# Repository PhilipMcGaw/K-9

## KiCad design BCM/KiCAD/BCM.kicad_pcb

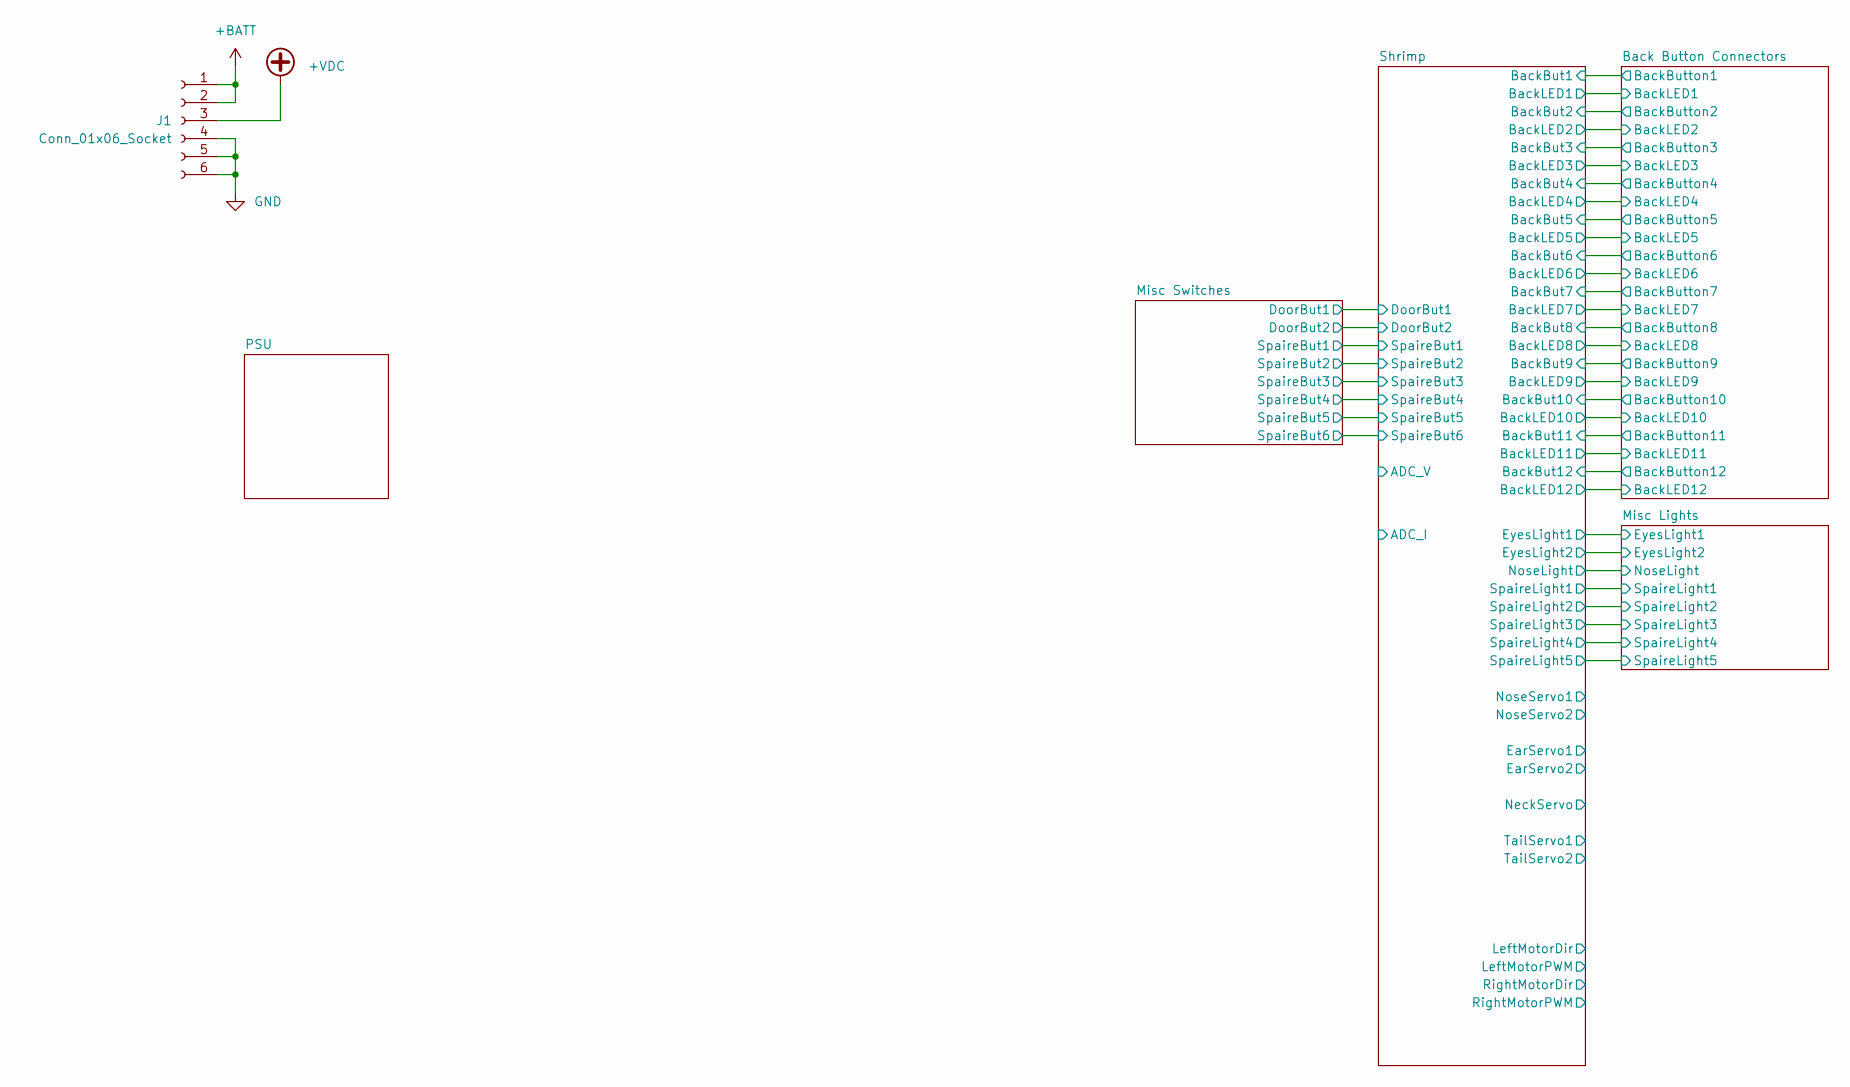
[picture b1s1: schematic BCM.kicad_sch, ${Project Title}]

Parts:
J1: Conn_01x06_Socket

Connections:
unnamed: J1.1, J1.2
unnamed: J1.4, J1.5, J1.6

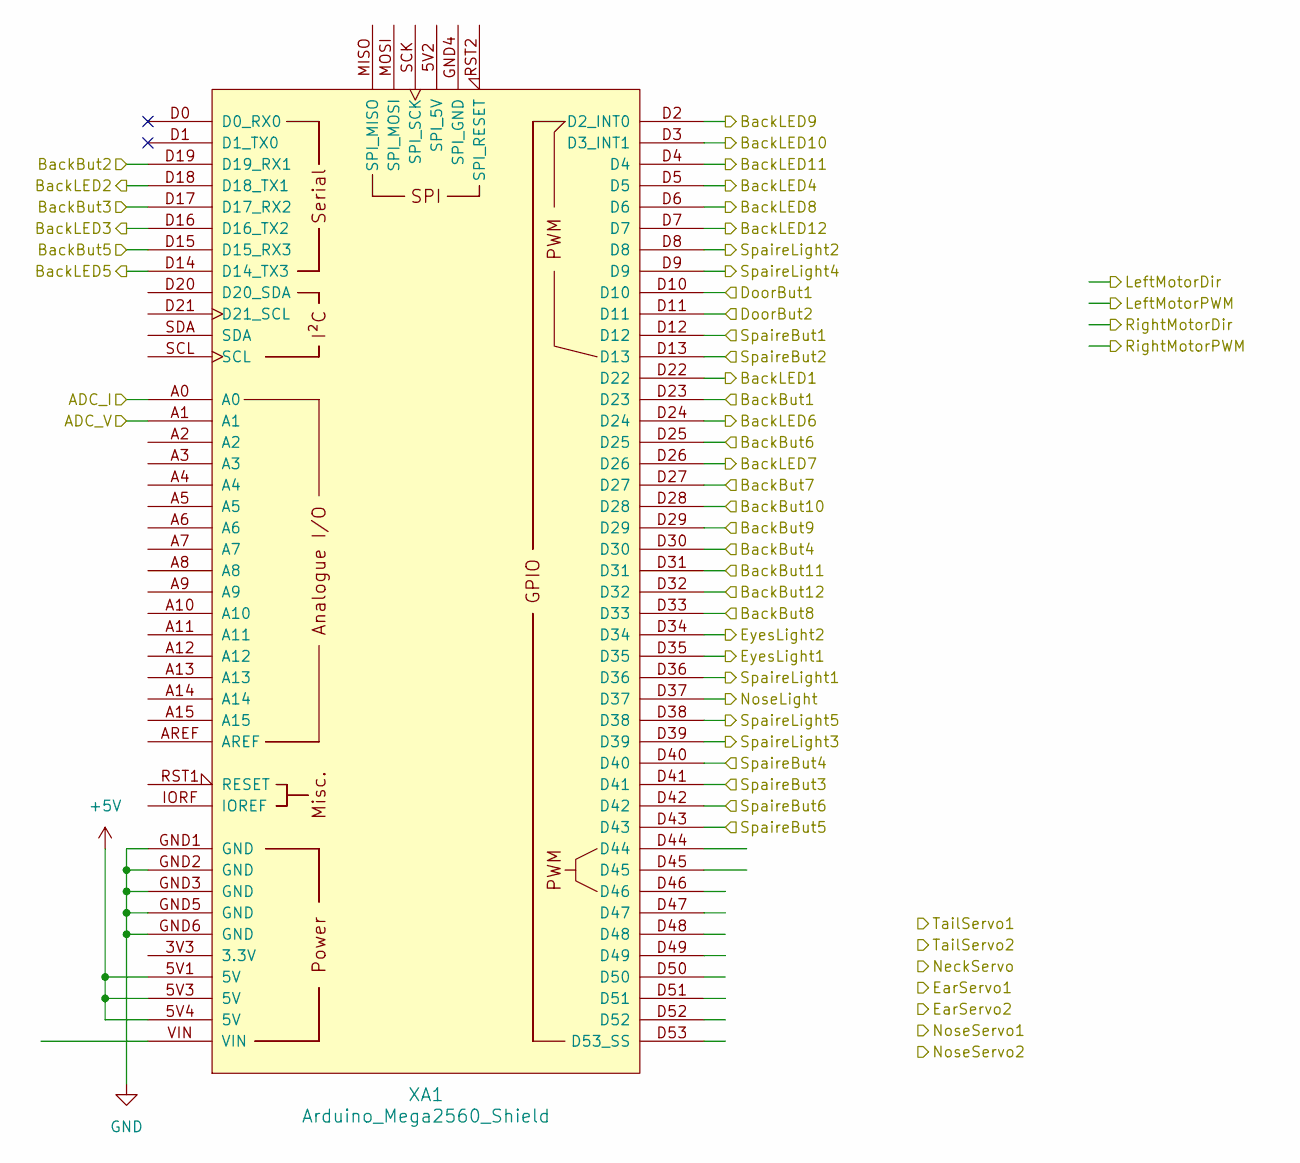
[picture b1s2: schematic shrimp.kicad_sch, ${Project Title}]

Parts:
XA1: Arduino_Mega2560_Shield

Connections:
+5V: XA1.5V1 (5V), XA1.5V3 (5V), XA1.5V4 (5V); also elsewhere on the board
/Back Button Connectors/BackButton1: XA1.D23; also elsewhere on the board
/Back Button Connectors/BackButton2: XA1.D19 (D19_RX1); also elsewhere on the board
/Back Button Connectors/BackButton3: XA1.D17 (D17_RX2); also elsewhere on the board
/Back Button Connectors/BackButton4: XA1.D30; also elsewhere on the board
/Back Button Connectors/BackButton5: XA1.D15 (D15_RX3); also elsewhere on the board
/Back Button Connectors/BackButton6: XA1.D25; also elsewhere on the board
/Back Button Connectors/BackButton7: XA1.D27; also elsewhere on the board
/Back Button Connectors/BackButton8: XA1.D33; also elsewhere on the board
/Back Button Connectors/BackButton9: XA1.D29; also elsewhere on the board
/Back Button Connectors/BackButton10: XA1.D28; also elsewhere on the board
/Back Button Connectors/BackButton11: XA1.D31; also elsewhere on the board
/Back Button Connectors/BackButton12: XA1.D32; also elsewhere on the board
/Back Button Connectors/BackLED1: XA1.D22; also elsewhere on the board
/Back Button Connectors/BackLED2: XA1.D18 (D18_TX1); also elsewhere on the board
/Back Button Connectors/BackLED3: XA1.D16 (D16_TX2); also elsewhere on the board
/Back Button Connectors/BackLED4: XA1.D5; also elsewhere on the board
/Back Button Connectors/BackLED5: XA1.D14 (D14_TX3); also elsewhere on the board
/Back Button Connectors/BackLED6: XA1.D24; also elsewhere on the board
/Back Button Connectors/BackLED7: XA1.D26; also elsewhere on the board
/Back Button Connectors/BackLED8: XA1.D6; also elsewhere on the board
/Back Button Connectors/BackLED9: XA1.D2 (D2_INT0); also elsewhere on the board
/Back Button Connectors/BackLED10: XA1.D3 (D3_INT1); also elsewhere on the board
/Back Button Connectors/BackLED11: XA1.D4; also elsewhere on the board
/Back Button Connectors/BackLED12: XA1.D7; also elsewhere on the board
/Misc Lights/EyesLight1: XA1.D35; also elsewhere on the board
/Misc Lights/EyesLight2: XA1.D34; also elsewhere on the board
/Misc Lights/NoseLight: XA1.D37; also elsewhere on the board
/Misc Lights/SpaireLight1: XA1.D36; also elsewhere on the board
/Misc Lights/SpaireLight2: XA1.D8; also elsewhere on the board
/Misc Lights/SpaireLight3: XA1.D39; also elsewhere on the board
/Misc Lights/SpaireLight4: XA1.D9; also elsewhere on the board
/Misc Lights/SpaireLight5: XA1.D38; also elsewhere on the board
/Misc Switches/DoorBut1: XA1.D10; also elsewhere on the board
/Misc Switches/DoorBut2: XA1.D11; also elsewhere on the board
/Misc Switches/SpaireBut1: XA1.D12; also elsewhere on the board
/Misc Switches/SpaireBut2: XA1.D13; also elsewhere on the board
/Misc Switches/SpaireBut3: XA1.D41; also elsewhere on the board
/Misc Switches/SpaireBut4: XA1.D40; also elsewhere on the board
/Misc Switches/SpaireBut5: XA1.D43; also elsewhere on the board
/Misc Switches/SpaireBut6: XA1.D42; also elsewhere on the board
/Shrimp/ADC_I: XA1.A0
/Shrimp/ADC_V: XA1.A1
/Shrimp/EarServo1: XA1.D50
/Shrimp/EarServo2: XA1.D51
/Shrimp/NeckServo: XA1.D49
/Shrimp/NoseServo1: XA1.D52
/Shrimp/NoseServo2: XA1.D53 (D53_SS)
/Shrimp/SpairServo1: XA1.D44
/Shrimp/SpairServo2: XA1.D45
/Shrimp/SpairServo3: XA1.D46
/Shrimp/TailServo1: XA1.D47
/Shrimp/TailServo2: XA1.D48
GND: XA1.GND1 (GND), XA1.GND2 (GND), XA1.GND3 (GND), XA1.GND5 (GND), XA1.GND6 (GND); also elsewhere on the board

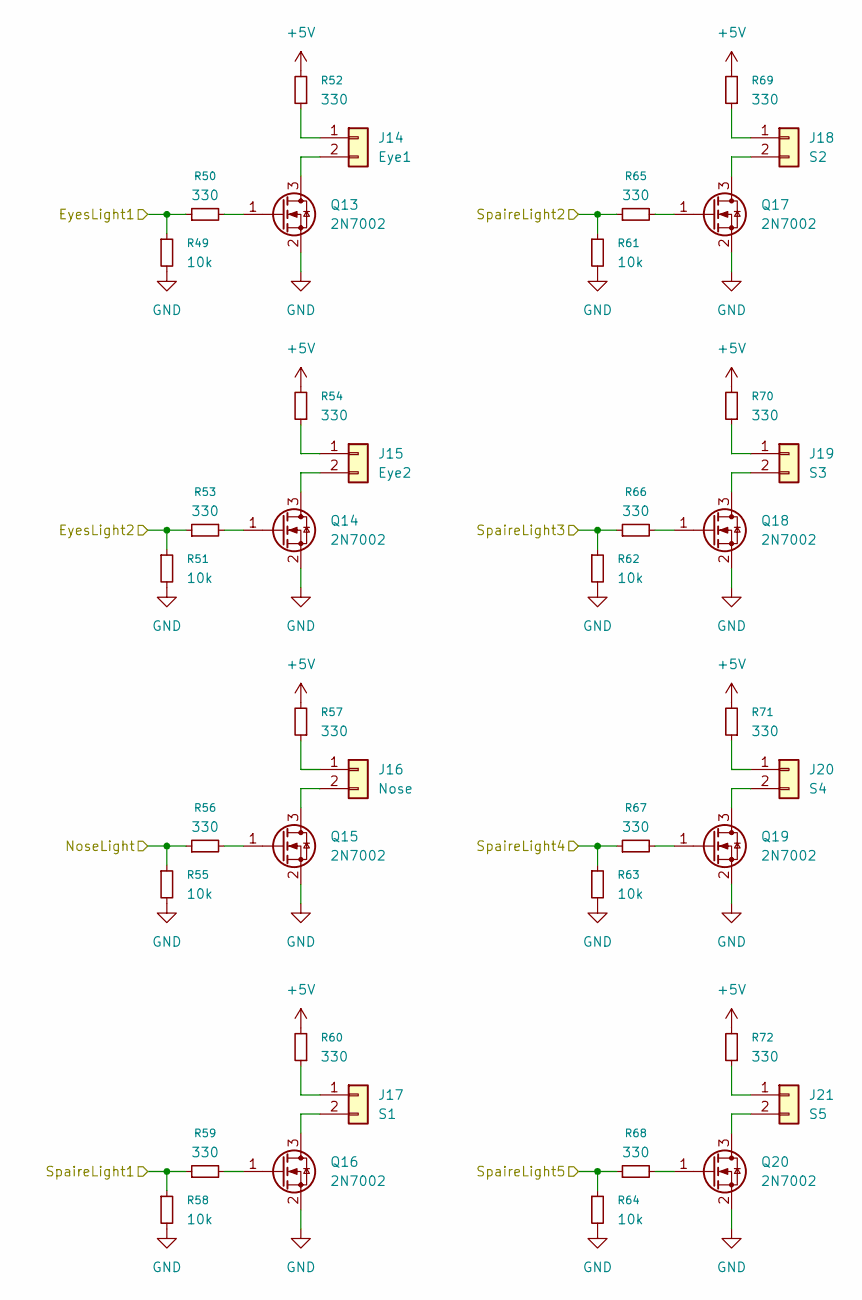
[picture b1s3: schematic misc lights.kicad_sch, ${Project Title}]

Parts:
J14: Eye1; JST_XA_B02B-XASK-1_1x02_P2.50mm_Vertical
J15: Eye2; JST_XA_B02B-XASK-1_1x02_P2.50mm_Vertical
J16: Nose; JST_XA_B02B-XASK-1_1x02_P2.50mm_Vertical
J17: S1; JST_XA_B02B-XASK-1_1x02_P2.50mm_Vertical
J18: S2; JST_XA_B02B-XASK-1_1x02_P2.50mm_Vertical
J19: S3; JST_XA_B02B-XASK-1_1x02_P2.50mm_Vertical
J20: S4; JST_XA_B02B-XASK-1_1x02_P2.50mm_Vertical
J21: S5; JST_XA_B02B-XASK-1_1x02_P2.50mm_Vertical
Q13, Q14, Q15, Q16, Q17, Q18, Q19, Q20: 2N7002; SOT-23
R49, R51, R55, R58, R61, R62, R63, R64: 10k; R_0805_2012Metric_Pad1.20x1.40mm_HandSolder
R50, R52, R53, R54, R56, R57, R59, R60, R65, R66, R67, R68, R69, R70, R71, R72: 330; R_0805_2012Metric_Pad1.20x1.40mm_HandSolder

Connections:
+5V: R52.2, R54.2, R57.2, R60.2, R69.2, R70.2, R71.2, R72.2; also elsewhere on the board
/Misc Lights/EyesLight1: R49.1, R50.1; also elsewhere on the board
/Misc Lights/EyesLight2: R51.1, R53.1; also elsewhere on the board
/Misc Lights/NoseLight: R55.1, R56.1; also elsewhere on the board
/Misc Lights/SpaireLight1: R58.1, R59.1; also elsewhere on the board
/Misc Lights/SpaireLight2: R61.1, R65.1; also elsewhere on the board
/Misc Lights/SpaireLight3: R62.1, R66.1; also elsewhere on the board
/Misc Lights/SpaireLight4: R63.1, R67.1; also elsewhere on the board
/Misc Lights/SpaireLight5: R64.1, R68.1; also elsewhere on the board
GND: Q13.2 (S), Q14.2 (S), Q15.2 (S), Q16.2 (S), Q17.2 (S), Q18.2 (S), Q19.2 (S), Q20.2 (S), R49.2, R51.2, R55.2, R58.2, R61.2, R62.2, R63.2, R64.2; also elsewhere on the board
unnamed: J14.1, R52.1
unnamed: J14.2, Q13.3 (D)
unnamed: J15.1, R54.1
unnamed: J15.2, Q14.3 (D)
unnamed: J16.1, R57.1
unnamed: J16.2, Q15.3 (D)
unnamed: J17.1, R60.1
unnamed: J17.2, Q16.3 (D)
unnamed: J18.1, R69.1
unnamed: J18.2, Q17.3 (D)
unnamed: J19.1, R70.1
unnamed: J19.2, Q18.3 (D)
unnamed: J20.1, R71.1
unnamed: J20.2, Q19.3 (D)
unnamed: J21.1, R72.1
unnamed: J21.2, Q20.3 (D)
unnamed: Q13.1 (G), R50.2
unnamed: Q14.1 (G), R53.2
unnamed: Q15.1 (G), R56.2
unnamed: Q16.1 (G), R59.2
unnamed: Q17.1 (G), R65.2
unnamed: Q18.1 (G), R66.2
unnamed: Q19.1 (G), R67.2
unnamed: Q20.1 (G), R68.2

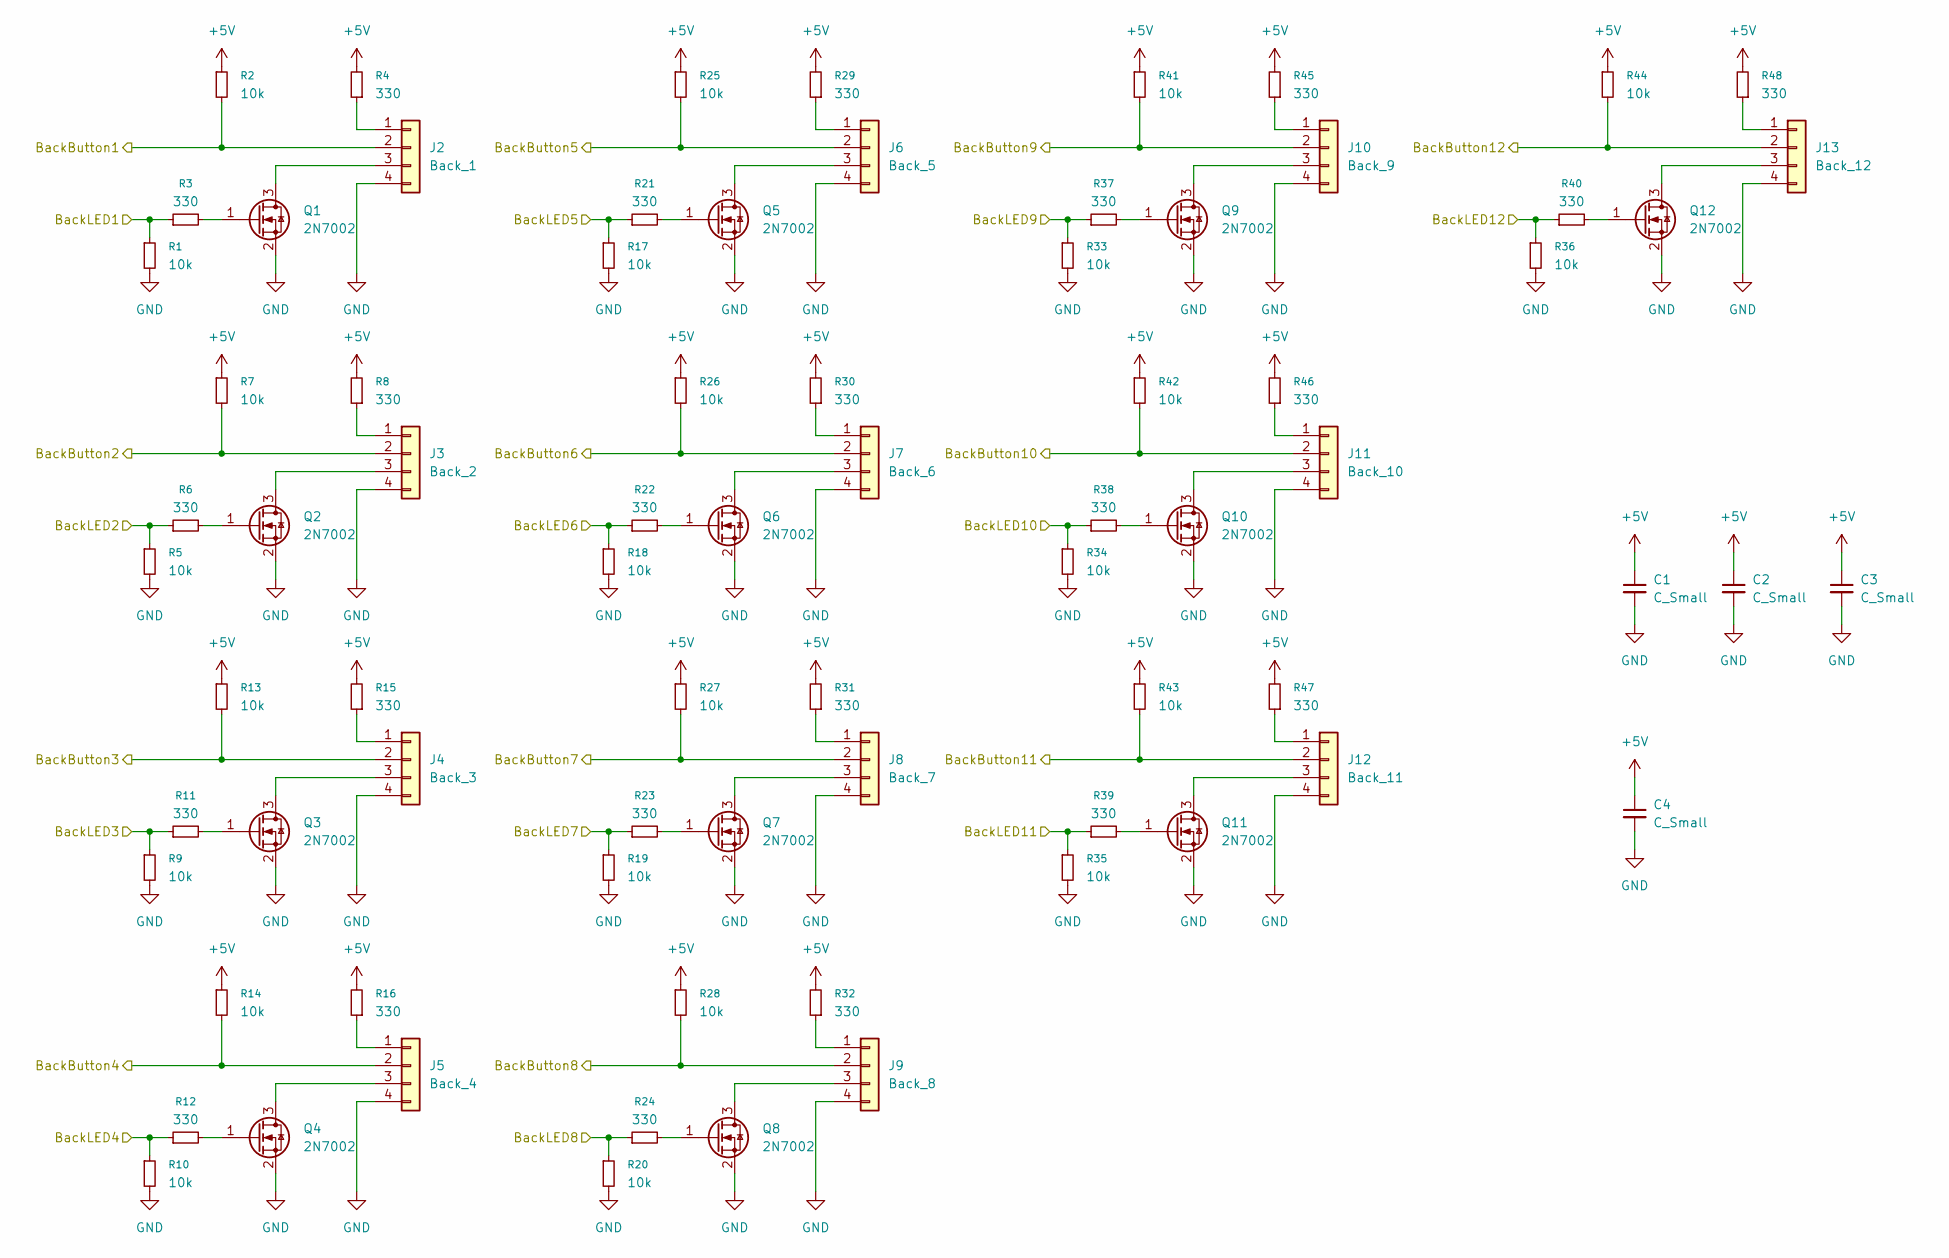
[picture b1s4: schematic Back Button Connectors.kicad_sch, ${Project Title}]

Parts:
C1, C2, C3, C4: C_Small; C_0805_2012Metric_Pad1.18x1.45mm_HandSolder
J2: Back_1; JST_XA_B04B-XASK-1_1x04_P2.50mm_Vertical
J3: Back_2; JST_XA_B04B-XASK-1_1x04_P2.50mm_Vertical
J4: Back_3; JST_XA_B04B-XASK-1_1x04_P2.50mm_Vertical
J5: Back_4; JST_XA_B04B-XASK-1_1x04_P2.50mm_Vertical
J6: Back_5; JST_XA_B04B-XASK-1_1x04_P2.50mm_Vertical
J7: Back_6; JST_XA_B04B-XASK-1_1x04_P2.50mm_Vertical
J8: Back_7; JST_XA_B04B-XASK-1_1x04_P2.50mm_Vertical
J9: Back_8; JST_XA_B04B-XASK-1_1x04_P2.50mm_Vertical
J10: Back_9; JST_XA_B04B-XASK-1_1x04_P2.50mm_Vertical
J11: Back_10; JST_XA_B04B-XASK-1_1x04_P2.50mm_Vertical
J12: Back_11; JST_XA_B04B-XASK-1_1x04_P2.50mm_Vertical
J13: Back_12; JST_XA_B04B-XASK-1_1x04_P2.50mm_Vertical
Q1, Q2, Q3, Q4, Q5, Q6, Q7, Q8, Q9, Q10, Q11, Q12: 2N7002; SOT-23
R1, R2, R5, R7, R9, R10, R13, R14, R17, R18, R19, R20, R25, R26, R27, R28, R33, R34, R35, R36, R41, R42, R43, R44: 10k; R_0805_2012Metric_Pad1.20x1.40mm_HandSolder
R3, R4, R6, R8, R11, R12, R15, R16, R21, R22, R23, R24, R29, R30, R31, R32, R37, R38, R39, R40, R45, R46, R47, R48: 330; R_0805_2012Metric_Pad1.20x1.40mm_HandSolder

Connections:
+5V: C1.1, C2.1, C3.1, C4.1, R2.1, R4.2, R7.1, R8.2, R13.1, R14.1, R15.2, R16.2, R25.1, R26.1, R27.1, R28.1, R29.2, R30.2, R31.2, R32.2, R41.1, R42.1, R43.1, R44.1, R45.2, R46.2, R47.2, R48.2; also elsewhere on the board
/Back Button Connectors/BackButton1: J2.2, R2.2; also elsewhere on the board
/Back Button Connectors/BackButton2: J3.2, R7.2; also elsewhere on the board
/Back Button Connectors/BackButton3: J4.2, R13.2; also elsewhere on the board
/Back Button Connectors/BackButton4: J5.2, R14.2; also elsewhere on the board
/Back Button Connectors/BackButton5: J6.2, R25.2; also elsewhere on the board
/Back Button Connectors/BackButton6: J7.2, R26.2; also elsewhere on the board
/Back Button Connectors/BackButton7: J8.2, R27.2; also elsewhere on the board
/Back Button Connectors/BackButton8: J9.2, R28.2; also elsewhere on the board
/Back Button Connectors/BackButton9: J10.2, R41.2; also elsewhere on the board
/Back Button Connectors/BackButton10: J11.2, R42.2; also elsewhere on the board
/Back Button Connectors/BackButton11: J12.2, R43.2; also elsewhere on the board
/Back Button Connectors/BackButton12: J13.2, R44.2; also elsewhere on the board
/Back Button Connectors/BackLED1: R1.1, R3.1; also elsewhere on the board
/Back Button Connectors/BackLED2: R5.1, R6.1; also elsewhere on the board
/Back Button Connectors/BackLED3: R9.1, R11.1; also elsewhere on the board
/Back Button Connectors/BackLED4: R10.1, R12.1; also elsewhere on the board
/Back Button Connectors/BackLED5: R17.1, R21.1; also elsewhere on the board
/Back Button Connectors/BackLED6: R18.1, R22.1; also elsewhere on the board
/Back Button Connectors/BackLED7: R19.1, R23.1; also elsewhere on the board
/Back Button Connectors/BackLED8: R20.1, R24.1; also elsewhere on the board
/Back Button Connectors/BackLED9: R33.1, R37.1; also elsewhere on the board
/Back Button Connectors/BackLED10: R34.1, R38.1; also elsewhere on the board
/Back Button Connectors/BackLED11: R35.1, R39.1; also elsewhere on the board
/Back Button Connectors/BackLED12: R36.1, R40.1; also elsewhere on the board
GND: C1.2, C2.2, C3.2, C4.2, J2.4, J3.4, J4.4, J5.4, J6.4, J7.4, J8.4, J9.4, J10.4, J11.4, J12.4, J13.4, Q1.2 (S), Q2.2 (S), Q3.2 (S), Q4.2 (S), Q5.2 (S), Q6.2 (S), Q7.2 (S), Q8.2 (S), Q9.2 (S), Q10.2 (S), Q11.2 (S), Q12.2 (S), R1.2, R5.2, R9.2, R10.2, R17.2, R18.2, R19.2, R20.2, R33.2, R34.2, R35.2, R36.2; also elsewhere on the board
unnamed: J2.1, R4.1
unnamed: J2.3, Q1.3 (D)
unnamed: J3.1, R8.1
unnamed: J3.3, Q2.3 (D)
unnamed: J4.1, R15.1
unnamed: J4.3, Q3.3 (D)
unnamed: J5.1, R16.1
unnamed: J5.3, Q4.3 (D)
unnamed: J6.1, R29.1
unnamed: J6.3, Q5.3 (D)
unnamed: J7.1, R30.1
unnamed: J7.3, Q6.3 (D)
unnamed: J8.1, R31.1
unnamed: J8.3, Q7.3 (D)
unnamed: J9.1, R32.1
unnamed: J9.3, Q8.3 (D)
unnamed: J10.1, R45.1
unnamed: J10.3, Q9.3 (D)
unnamed: J11.1, R46.1
unnamed: J11.3, Q10.3 (D)
unnamed: J12.1, R47.1
unnamed: J12.3, Q11.3 (D)
unnamed: J13.1, R48.1
unnamed: J13.3, Q12.3 (D)
unnamed: Q1.1 (G), R3.2
unnamed: Q2.1 (G), R6.2
unnamed: Q3.1 (G), R11.2
unnamed: Q4.1 (G), R12.2
unnamed: Q5.1 (G), R21.2
unnamed: Q6.1 (G), R22.2
unnamed: Q7.1 (G), R23.2
unnamed: Q8.1 (G), R24.2
unnamed: Q9.1 (G), R37.2
unnamed: Q10.1 (G), R38.2
unnamed: Q11.1 (G), R39.2
unnamed: Q12.1 (G), R40.2

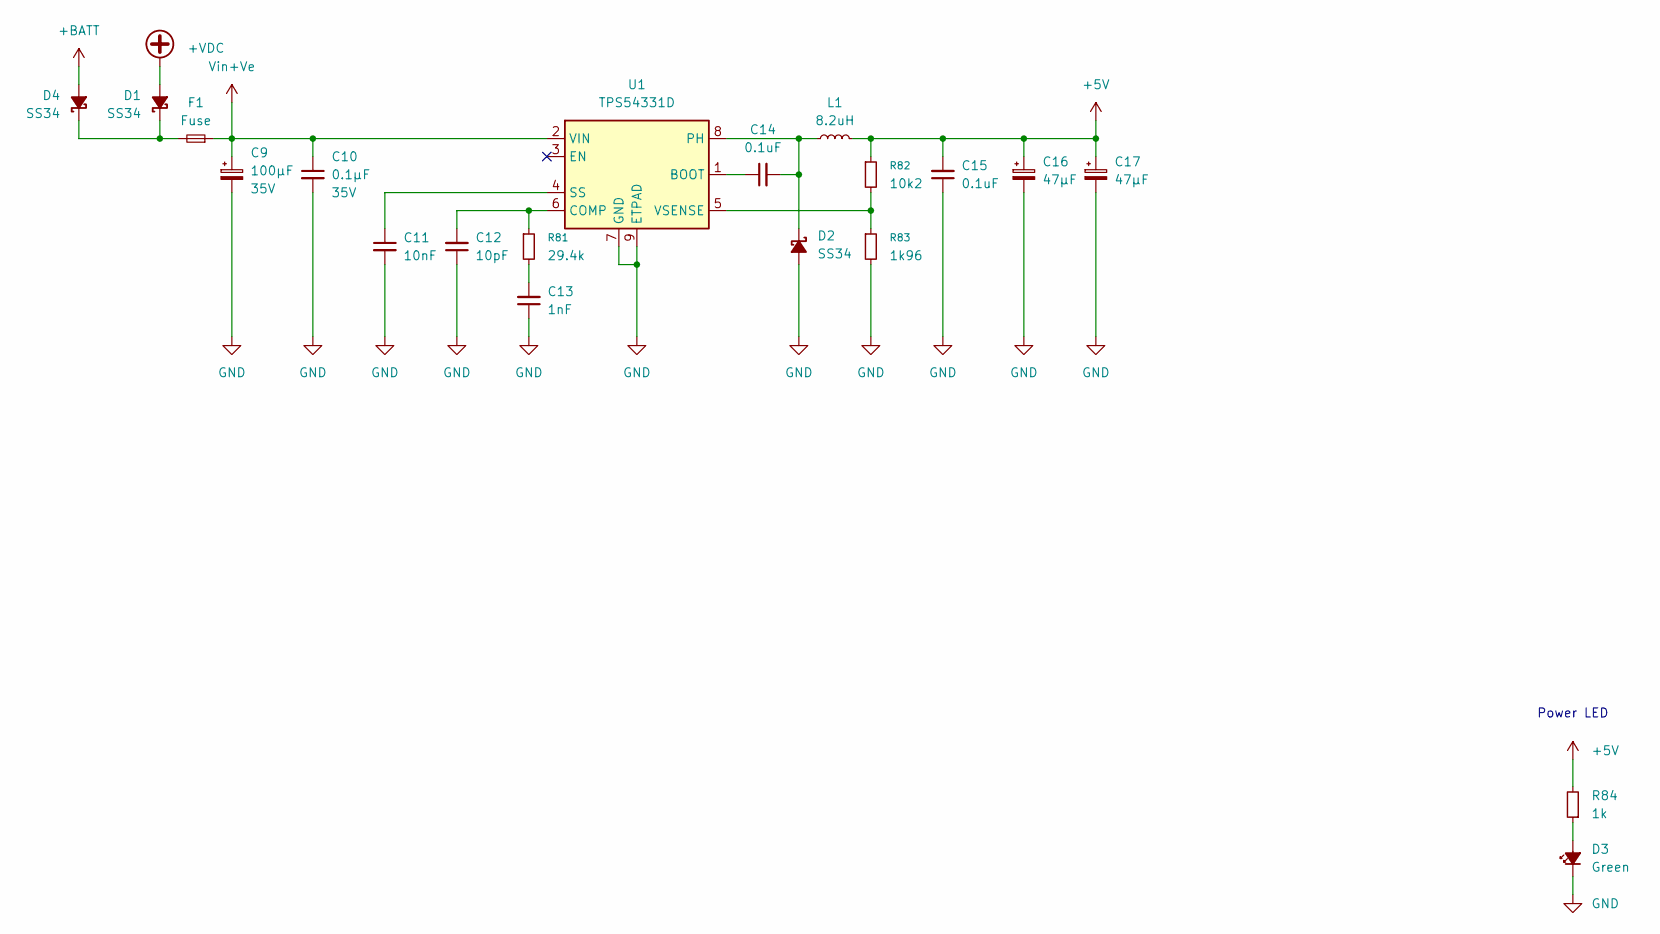
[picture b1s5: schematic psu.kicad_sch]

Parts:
C9: 100μF; CP_Elec_5x5.9; Voltage 35V; Farnell 2690258
C10: 0.1μF; C_0805_2012Metric_Pad1.18x1.45mm_HandSolder; Voltage 35V; Farnell 2773206
C11: 10nF; C_0805_2012Metric_Pad1.18x1.45mm_HandSolder
C12: 10pF; C_0805_2012Metric_Pad1.18x1.45mm_HandSolder
C13: 1nF; C_0805_2012Metric_Pad1.18x1.45mm_HandSolder
C14, C15: 0.1uF; C_0805_2012Metric_Pad1.18x1.45mm_HandSolder
C16, C17: 47μF; CP_Elec_5x5.9
D1, D2, D4: SS34; D_SMA_Handsoldering; farnell 2675144
D3: Green; D_0805_2012Metric_Pad1.15x1.40mm_HandSolder
F1: Fuse; Fuse_2010_5025Metric_Pad1.52x2.65mm_HandSolder
L1: 8.2uH; Farnell 2709611
R81: 29.4k
R82: 10k2
R83: 1k96
R84: 1k; R_0805_2012Metric_Pad1.20x1.40mm_HandSolder
U1: TPS54331D; TI_SO-PowerPAD-8_ThermalVias

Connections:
+5V: C15.2, C16.1, C17.1, L1.2, R82.1, R84.2; also elsewhere on the board
+BATT: D4.2 (A); also elsewhere on the board
+VDC: D1.2 (A); also elsewhere on the board
GND: C9.2, C10.2, C11.2, C12.1, C13.1, C15.1, C16.2, C17.2, D2.2 (A), D3.1 (K), R83.2, U1.7 (GND), U1.9 (ETPAD); also elsewhere on the board
unnamed: C13.2, R81.2
unnamed: C14.2, D2.1 (K), L1.1, U1.8 (PH)
unnamed: D3.2 (A), R84.1
unnamed: C14.1, U1.1 (BOOT)
unnamed: C12.2, R81.1, U1.6 (COMP)
unnamed: C11.1, U1.4 (SS)
unnamed: R82.2, R83.1, U1.5 (VSENSE)
Vin+Ve: D1.1 (K), D4.1 (K), F1.2
Vin+Ve (fused): C9.1, C10.1, F1.1, U1.2 (VIN)

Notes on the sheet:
Power LED

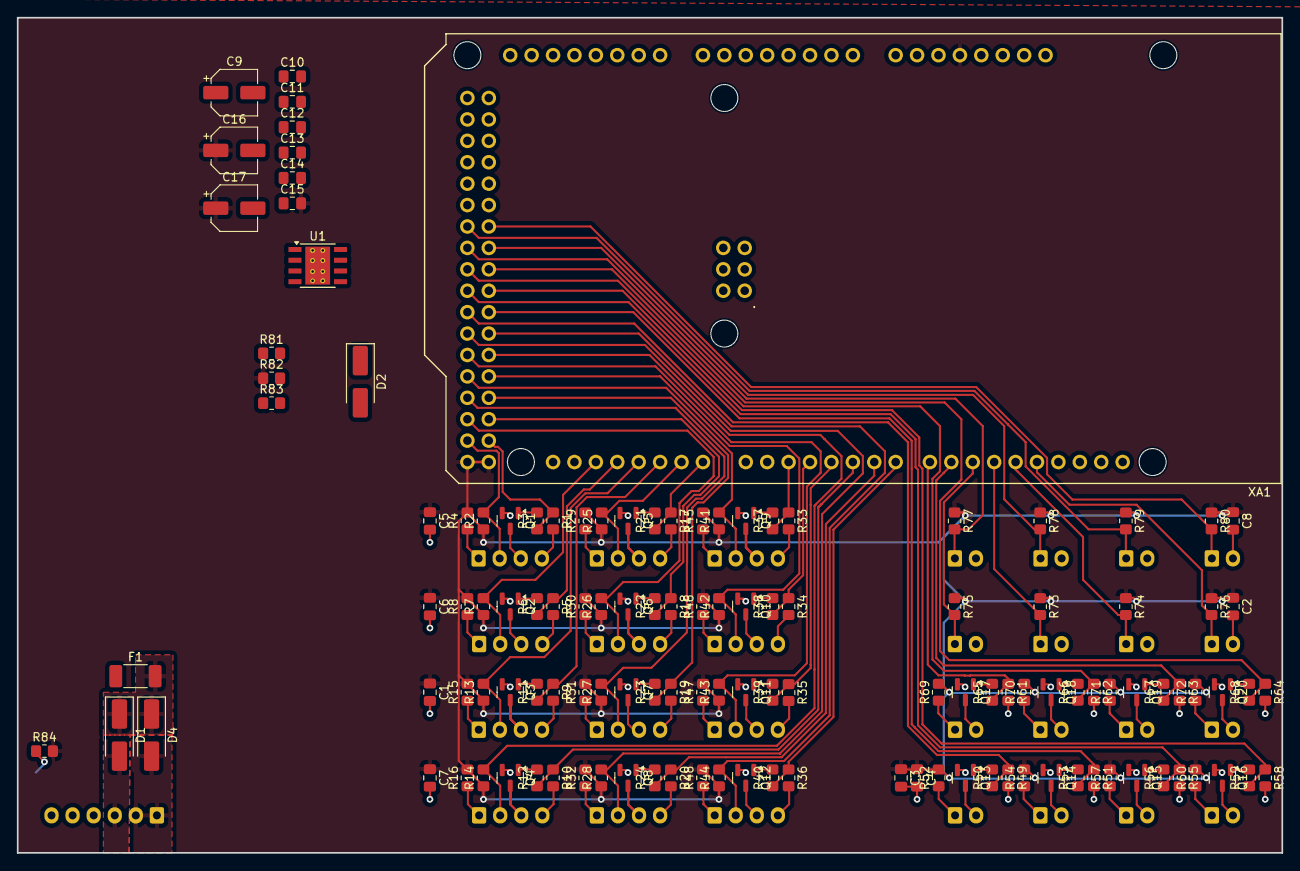
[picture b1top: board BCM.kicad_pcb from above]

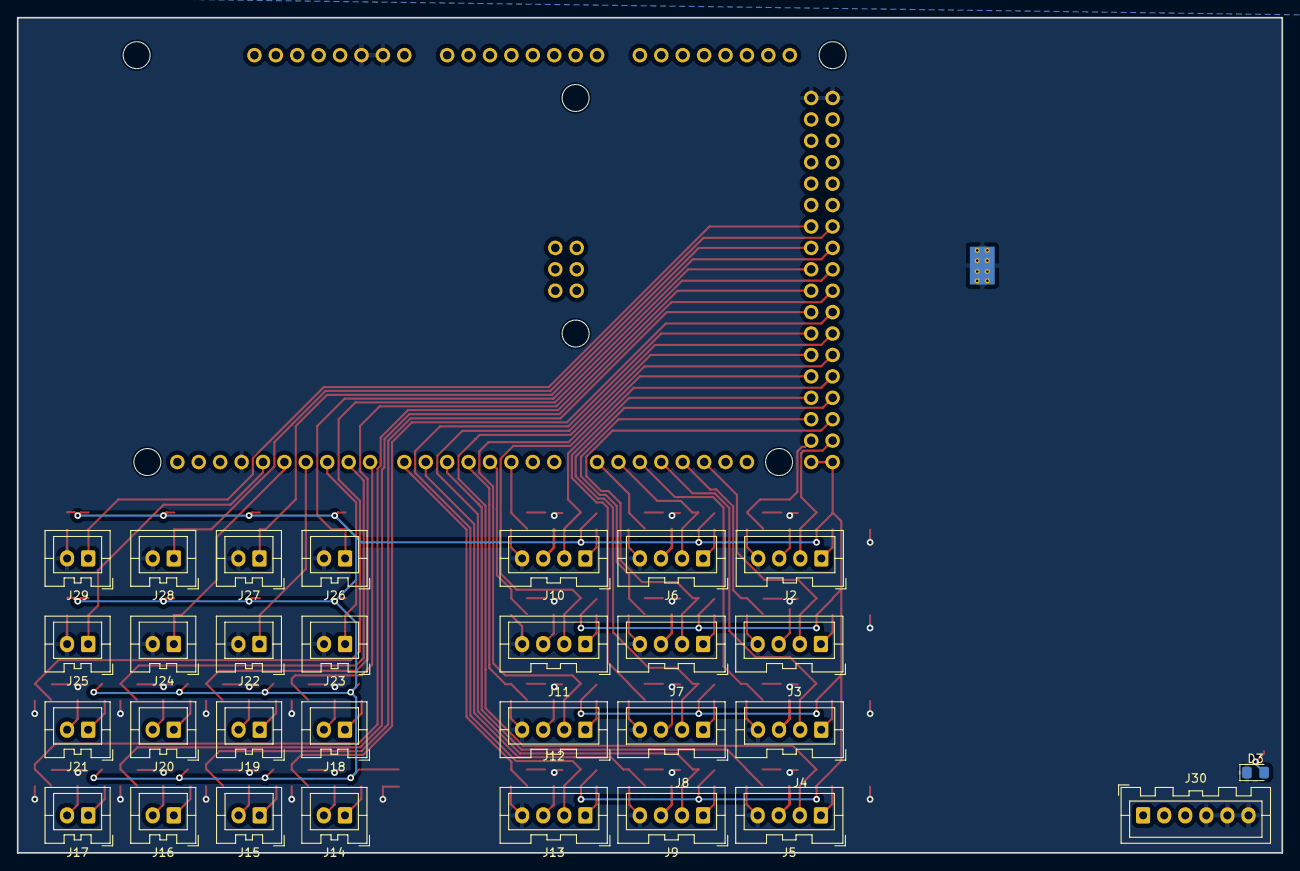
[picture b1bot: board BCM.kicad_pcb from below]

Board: 2 copper layers, 150.0 x 99.1 mm, 157 parts (30 on the bottom side), 113 nets.

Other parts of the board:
C5, C6, C7, C8: C_Small; C_0805_2012Metric_Pad1.18x1.45mm_HandSolder
J22: Door2; JST_XA_B02B-XASK-1_1x02_P2.50mm_Vertical
J23: Door1; JST_XA_B02B-XASK-1_1x02_P2.50mm_Vertical
J24: But1; JST_XA_B02B-XASK-1_1x02_P2.50mm_Vertical
J25: But2; JST_XA_B02B-XASK-1_1x02_P2.50mm_Vertical
J26: But3; JST_XA_B02B-XASK-1_1x02_P2.50mm_Vertical
J27: But4; JST_XA_B02B-XASK-1_1x02_P2.50mm_Vertical
J28: But5; JST_XA_B02B-XASK-1_1x02_P2.50mm_Vertical
J29: But6; JST_XA_B02B-XASK-1_1x02_P2.50mm_Vertical
J30: Power; JST_XA_B06B-XASK-1_1x06_P2.50mm_Vertical
R73, R74, R75, R76, R77, R78, R79, R80: 10k; R_0805_2012Metric_Pad1.20x1.40mm_HandSolder

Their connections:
+5V: C5.1, C6.1, C7.1, C8.1, R73.1, R74.1, R75.1, R76.1, R77.1, R78.1, R79.1, R80.1; also elsewhere on the board
+BATT: J30.1, J30.2; also elsewhere on the board
+VDC: J30.3; also elsewhere on the board
/Misc Switches/DoorBut1: J23.1, R75.2; also elsewhere on the board
/Misc Switches/DoorBut2: J22.1, R73.2; also elsewhere on the board
/Misc Switches/SpaireBut1: J24.1, R74.2; also elsewhere on the board
/Misc Switches/SpaireBut2: J25.1, R76.2; also elsewhere on the board
/Misc Switches/SpaireBut3: J26.1, R77.2; also elsewhere on the board
/Misc Switches/SpaireBut4: J27.1, R78.2; also elsewhere on the board
/Misc Switches/SpaireBut5: J28.1, R79.2; also elsewhere on the board
/Misc Switches/SpaireBut6: J29.1, R80.2; also elsewhere on the board
GND: C5.2, C6.2, C7.2, C8.2, J22.2, J23.2, J24.2, J25.2, J26.2, J27.2, J28.2, J29.2, J30.4, J30.5, J30.6; also elsewhere on the board

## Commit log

2025-07-26 stop the STLs from being added
2025-07-26 Started kicad
2025-07-26 text vars
2025-07-26 text vars need fixed
2025-08-18 remove git modules
2025-08-27 started
2025-08-27 work
2025-09-06 added arduino
2025-09-07 some updates
2025-09-08 SDA SCL recovered
2025-09-08 added servos
2025-09-08 move buttons to own supply rail
2025-09-14 Sound Files added
2025-11-01 Well that kind of makes sense!
2026-03-03 clean up
